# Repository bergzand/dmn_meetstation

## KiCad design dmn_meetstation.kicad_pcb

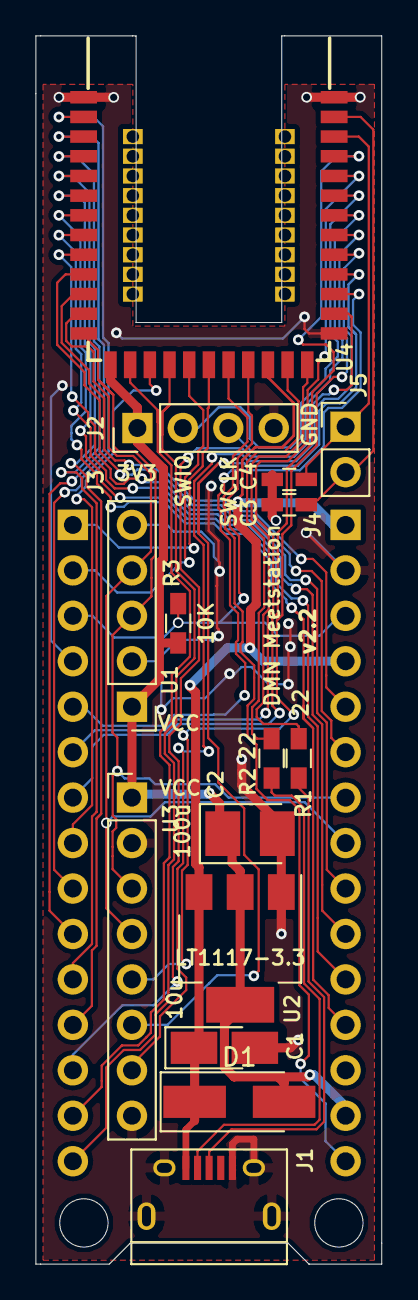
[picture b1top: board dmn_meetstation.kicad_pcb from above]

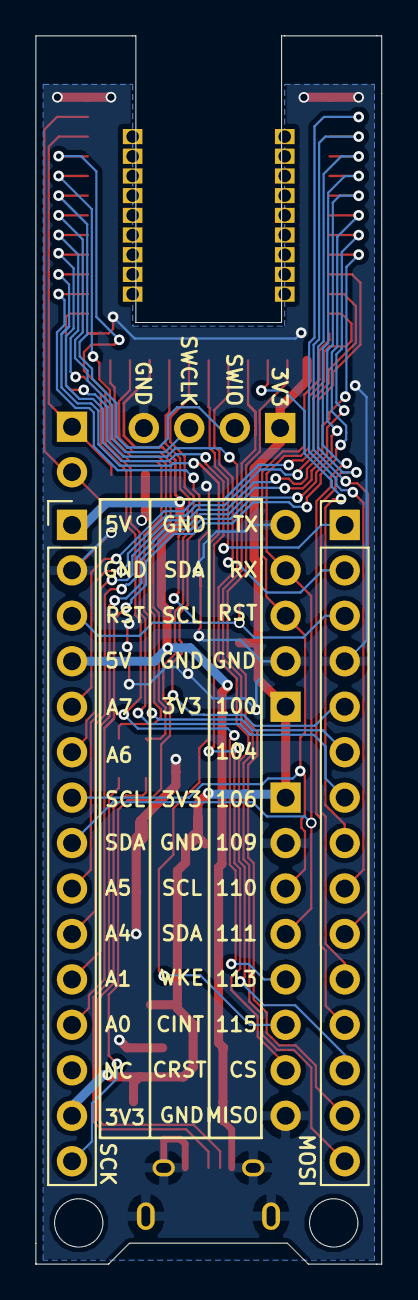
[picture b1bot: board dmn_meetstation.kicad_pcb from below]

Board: 2 copper layers, 19.3 x 68.6 mm, 19 parts (2 on the bottom side), 37 nets.

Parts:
C1: 10u; CP_Tantalum_Case-R_EIA-2012-12_Hand
C2: 100u; CP_Tantalum_Case-T_EIA-3528-12_Reflow
C3, C4: C; C_0603_HandSoldering
D1: 1N4007; D_SMA_Handsoldering
J1: USB_OTG; USB_Micro-B
J2: Conn_01x04; Pin_Header_Straight_1x04_Pitch2.54mm
J3, J4: Conn_01x15; Socket_Strip_Straight_1x15_Pitch2.54mm
J5: Conn_01x02; Pin_Header_Straight_1x02_Pitch2.54mm
MH1, MH2: MountingHole; MountingHole_2.7mm_M2.5
R1, R2: 22; R_0603_HandSoldering
R3: 10K; R_0603_HandSoldering
U1: bh1750breakout; Pin_Header_Straight_1x05_Pitch2.54mm
U2: LT1117-3.3; SOT-223-3_TabPin2
U3: CJMCU-8118; Pin_Header_Straight_1x08_Pitch2.54mm
U4: holyiot18010

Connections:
+3V3: C2.1, D1.2, J2.1, J4.14, R3.1, U1.1, U2.2, U3.1, U4.55
+5V: C1.1, D1.1, J1.1, J4.1, J4.4, U2.3, U4.47
/AIN0: J4.12, U4.7
/AIN1: J4.11, U4.6
/AIN4: J4.10, U4.8
/AIN5: J4.9, U4.9
/AIN6: J4.6, U4.10
/AIN7: J4.5, U4.11
/CJINT: U3.6, U4.41
/CJRESET: U3.7, U4.40
/CJWAKE: U3.5, U4.39
/I2CSCL: J4.7, U1.3, U3.3, U4.13
/I2CSDA: J4.8, U1.4, U3.4, U4.12
/NFC1: C4.1, J5.1, U4.34
/NFC2: C3.1, J5.2, U4.33
/P1.00: J3.5, U4.42
/P1.04: J3.6, U4.36
/P1.06: J3.7, U4.35
/P1.09: J3.8, U4.53
/P1.10: J3.9, U4.2
/P1.11: J3.10, U4.3
/P1.13: J3.11, U4.4
/P1.15: J3.12, U4.5
/RX: J3.2, U4.51
/SPICS: J3.13, U4.43
/SPIMISO: J3.14, U4.54
/SPIMOSI: J3.15, U4.52
/SPISCK: J4.15, U4.49
/SWDCLK: J2.3, U4.38
/SWDIO: J2.2, U4.37
/TX: J3.1, U4.50
/USB+: R1.1, U4.45
/USB-: R2.1, U4.46
/nRESET: J3.3, J4.3, R3.2, U4.48
GND: C1.2, C2.2, C3.2, C4.2, J1.5, J1.6, J2.4, J3.4, J4.2, U1.2, U1.5, U2.1, U3.2, U3.8, U4.1
unnamed: J1.2, R2.2
unnamed: J1.3, R1.2

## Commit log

2018-09-23 Cleanup, more groundplane
2018-09-23 Finalize short version layout
2018-09-23 more compact
2018-09-23 Shorter pcb version
2018-09-23 add holyiot library
2018-09-24 sch: change holes to M2.5
2018-09-24 Cleanup
2018-09-25 Rescue component
2018-09-25 Reroute to 5 mil min width
2018-09-25 update diode footprint
2018-09-26 More cleanup
2018-09-27 Add pdf version of schematic
